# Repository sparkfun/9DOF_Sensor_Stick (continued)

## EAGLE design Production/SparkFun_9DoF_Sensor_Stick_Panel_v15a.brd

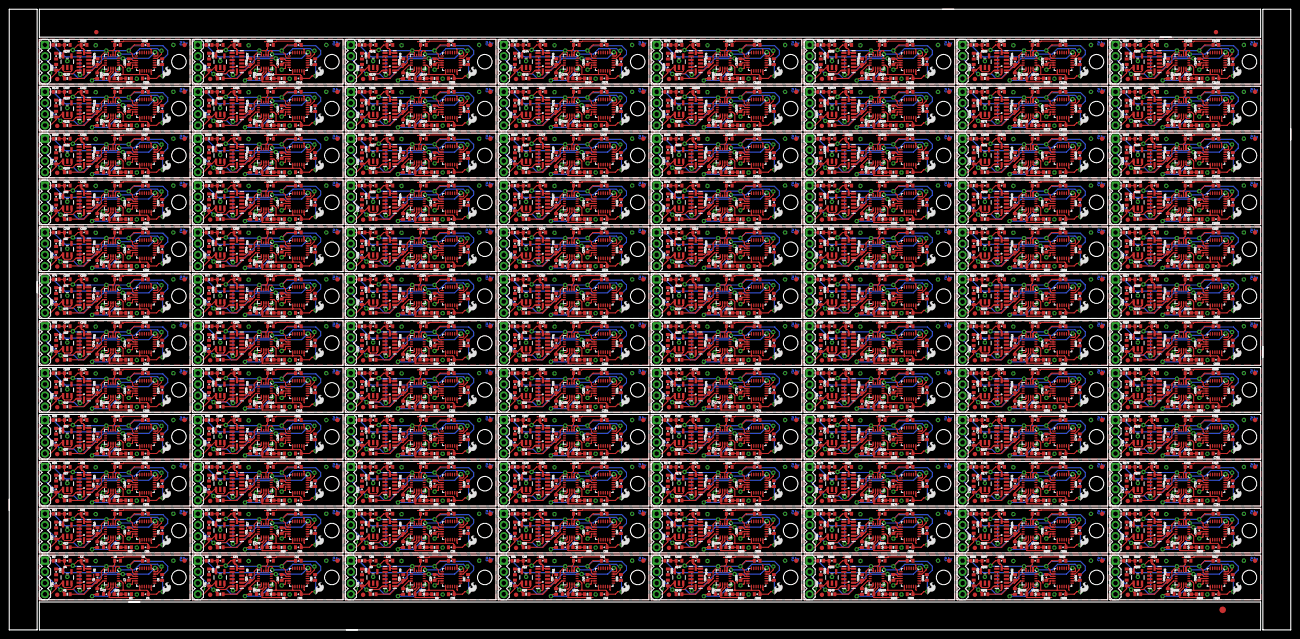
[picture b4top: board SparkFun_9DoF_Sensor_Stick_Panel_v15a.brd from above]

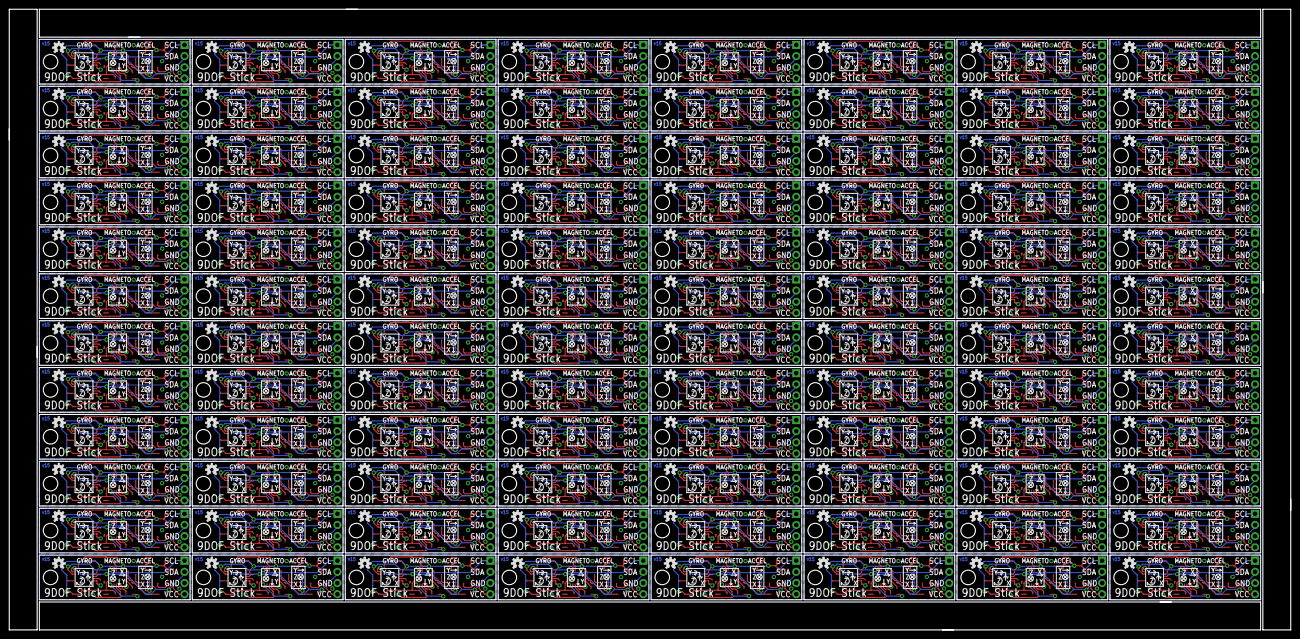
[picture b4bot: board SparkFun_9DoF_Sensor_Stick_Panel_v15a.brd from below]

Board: 2 copper layers, 291.6 x 141.2 mm, 2499 parts (96 on the bottom side), 1056 nets.

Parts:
C1, C2, C5, C7, C9, C10, C13, C14, C16, C18, C19, C24, C25, C26, C28, C30, C31, C36, C37, C38, C40, C42, C43, C48, C49, C50, C52, C54, C55, C60, C61, C62, C64, C66, C67, C72, C73, C74, C76, C78, C79, C84, C85, C86, C88, C90, C91, C96, C97, C98, C100, C102, C103, C108, C109, C110, C112, C114, C115, C120, C121, C122, C124, C126, C127, C132, C133, C134, C136, C138, C139, C144, C145, C146, C148, C150, C151, C156, C157, C158, C160, C162, C163, C168, C169, C170, C172, C174, C175, C180, C181, C182, C184, C186, C187, C192, C193, C194, C196, C198, C199, C204, C205, C206, C208, C210, C211, C216, C217, C218, C220, C222, C223, C228, C229, C230, C232, C234, C235, C240, C241, C242, C244, C246, C247, C252, C253, C254, C256, C258, C259, C264, C265, C266, C268, C270, C271, C276, C277, C278, C280, C282, C283, C288, C289, C290, C292, C294, C295, C300, C301, C302, C304, C306, C307, C312, C313, C314, C316, C318, C319, C324, C325, C326, C328, C330, C331, C336, C337, C338, C340, C342, C343, C348, C349, C350, C352, C354, C355, C360, C361, C362, C364, C366, C367, C372, C373, C374, C376, C378, C379, C384, C385, C386, C388, C390, C391, C396, C397, C398, C400, C402, C403, C408, C409, C410, C412, C414, C415, C420, C421, C422, C424, C426, C427, C432, C433, C434, C436, C438, C439, C444, C445, C446, C448, C450, C451, C456, C457, C458, C460, C462, C463, C468, C469, C470, C472, C474, C475, C480, C481, C482, C484, C486, C487, C492, C493, C494, C496, C498, C499, C504, C505, C506, C508, C510, C511, C516, C517, C518, C520, C522, C523, C528, C529, C530, C532, C534, C535, C540, C541, C542, C544, C546, C547, C552, C553, C554, C556, C558, C559, C564, C565, C566, C568, C570, C571, C576, C577, C578, C580, C582, C583, C588, C589, C590, C592, C594, C595, C600, C601, C602, C604, C606, C607, C612, C613, C614, C616, C618, C619, C624, C625, C626, C628, C630, C631, C636, C637, C638, C640, C642, C643, C648, C649, C650, C652, C654, C655, C660, C661, C662, C664, C666, C667, C672, C673, C674, C676, C678, C679, C684, C685, C686, C688, C690, C691, C696, C697, C698, C700, C702, C703, C708, C709, C710, C712, C714, C715, C720, C721, C722, C724, C726, C727, C732, C733, C734, C736, C738, C739, C744, C745, C746, C748, C750, C751, C756, C757, C758, C760, C762, C763, C768, C769, C770, C772, C774, C775, C780, C781, C782, C784, C786, C787, C792, C793, C794, C796, C798, C799, C804, C805, C806, C808, C810, C811, C816, C817, C818, C820, C822, C823, C828, C829, C830, C832, C834, C835, C840, C841, C842, C844, C846, C847, C852, C853, C854, C856, C858, C859, C864, C865, C866, C868, C870, C871, C876, C877, C878, C880, C882, C883, C888, C889, C890, C892, C894, C895, C900, C901, C902, C904, C906, C907, C912, C913, C914, C916, C918, C919, C924, C925, C926, C928, C930, C931, C936, C937, C938, C940, C942, C943, C948, C949, C950, C952, C954, C955, C960, C961, C962, C964, C966, C967, C972, C973, C974, C976, C978, C979, C984, C985, C986, C988, C990, C991, C996, C997, C998, C1000, C1002, C1003, C1008, C1009, C1010, C1012, C1014, C1015, C1020, C1021, C1022, C1024, C1026, C1027, C1032, C1033, C1034, C1036, C1038, C1039, C1044, C1045, C1046, C1048, C1050, C1051, C1056, C1057, C1058, C1060, C1062, C1063, C1068, C1069, C1070, C1072, C1074, C1075, C1080, C1081, C1082, C1084, C1086, C1087, C1092, C1093, C1094, C1096, C1098, C1099, C1104, C1105, C1106, C1108, C1110, C1111, C1116, C1117, C1118, C1120, C1122, C1123, C1128, C1129, C1130, C1132, C1134, C1135, C1140, C1141, C1142, C1144, C1146, C1147, C1152: 0.1uF; 0402-CAP
C3, C11, C12, C20, C21, C22, C32, C33, C34, C44, C45, C46, C56, C57, C58, C68, C69, C70, C80, C81, C82, C92, C93, C94, C104, C105, C106, C116, C117, C118, C128, C129, C130, C140, C141, C142, C152, C153, C154, C164, C165, C166, C176, C177, C178, C188, C189, C190, C200, C201, C202, C212, C213, C214, C224, C225, C226, C236, C237, C238, C248, C249, C250, C260, C261, C262, C272, C273, C274, C284, C285, C286, C296, C297, C298, C308, C309, C310, C320, C321, C322, C332, C333, C334, C344, C345, C346, C356, C357, C358, C368, C369, C370, C380, C381, C382, C392, C393, C394, C404, C405, C406, C416, C417, C418, C428, C429, C430, C440, C441, C442, C452, C453, C454, C464, C465, C466, C476, C477, C478, C488, C489, C490, C500, C501, C502, C512, C513, C514, C524, C525, C526, C536, C537, C538, C548, C549, C550, C560, C561, C562, C572, C573, C574, C584, C585, C586, C596, C597, C598, C608, C609, C610, C620, C621, C622, C632, C633, C634, C644, C645, C646, C656, C657, C658, C668, C669, C670, C680, C681, C682, C692, C693, C694, C704, C705, C706, C716, C717, C718, C728, C729, C730, C740, C741, C742, C752, C753, C754, C764, C765, C766, C776, C777, C778, C788, C789, C790, C800, C801, C802, C812, C813, C814, C824, C825, C826, C836, C837, C838, C848, C849, C850, C860, C861, C862, C872, C873, C874, C884, C885, C886, C896, C897, C898, C908, C909, C910, C920, C921, C922, C932, C933, C934, C944, C945, C946, C956, C957, C958, C968, C969, C970, C980, C981, C982, C992, C993, C994, C1004, C1005, C1006, C1016, C1017, C1018, C1028, C1029, C1030, C1040, C1041, C1042, C1052, C1053, C1054, C1064, C1065, C1066, C1076, C1077, C1078, C1088, C1089, C1090, C1100, C1101, C1102, C1112, C1113, C1114, C1124, C1125, C1126, C1136, C1137, C1138, C1148, C1149, C1150: 4.7uF; 0402-CAP
C4, C23, C35, C47, C59, C71, C83, C95, C107, C119, C131, C143, C155, C167, C179, C191, C203, C215, C227, C239, C251, C263, C275, C287, C299, C311, C323, C335, C347, C359, C371, C383, C395, C407, C419, C431, C443, C455, C467, C479, C491, C503, C515, C527, C539, C551, C563, C575, C587, C599, C611, C623, C635, C647, C659, C671, C683, C695, C707, C719, C731, C743, C755, C767, C779, C791, C803, C815, C827, C839, C851, C863, C875, C887, C899, C911, C923, C935, C947, C959, C971, C983, C995, C1007, C1019, C1031, C1043, C1055, C1067, C1079, C1091, C1103, C1115, C1127, C1139, C1151: 0.22uF; 0402-CAP
C6, C15, C27, C39, C51, C63, C75, C87, C99, C111, C123, C135, C147, C159, C171, C183, C195, C207, C219, C231, C243, C255, C267, C279, C291, C303, C315, C327, C339, C351, C363, C375, C387, C399, C411, C423, C435, C447, C459, C471, C483, C495, C507, C519, C531, C543, C555, C567, C579, C591, C603, C615, C627, C639, C651, C663, C675, C687, C699, C711, C723, C735, C747, C759, C771, C783, C795, C807, C819, C831, C843, C855, C867, C879, C891, C903, C915, C927, C939, C951, C963, C975, C987, C999, C1011, C1023, C1035, C1047, C1059, C1071, C1083, C1095, C1107, C1119, C1131, C1143: 2.2nF; 0402-CAP
C8, C17, C29, C41, C53, C65, C77, C89, C101, C113, C125, C137, C149, C161, C173, C185, C197, C209, C221, C233, C245, C257, C269, C281, C293, C305, C317, C329, C341, C353, C365, C377, C389, C401, C413, C425, C437, C449, C461, C473, C485, C497, C509, C521, C533, C545, C557, C569, C581, C593, C605, C617, C629, C641, C653, C665, C677, C689, C701, C713, C725, C737, C749, C761, C773, C785, C797, C809, C821, C833, C845, C857, C869, C881, C893, C905, C917, C929, C941, C953, C965, C977, C989, C1001, C1013, C1025, C1037, C1049, C1061, C1073, C1085, C1097, C1109, C1121, C1133, C1145: 10nF; 0402-CAP
E$1: FIDUCIAL-1.5X3
E$5, E$6: FIDUCIAL-1X2
JP1, JP2, JP9, JP10, JP14, JP15, JP19, JP20, JP24, JP25, JP29, JP30, JP34, JP35, JP39, JP40, JP44, JP45, JP49, JP50, JP54, JP55, JP59, JP60, JP64, JP65, JP69, JP70, JP74, JP75, JP79, JP80, JP84, JP85, JP89, JP90, JP94, JP95, JP99, JP100, JP104, JP105, JP109, JP110, JP114, JP115, JP119, JP120, JP124, JP125, JP129, JP130, JP134, JP135, JP139, JP140, JP144, JP145, JP149, JP150, JP154, JP155, JP159, JP160, JP164, JP165, JP169, JP170, JP174, JP175, JP179, JP180, JP184, JP185, JP189, JP190, JP194, JP195, JP199, JP200, JP204, JP205, JP209, JP210, JP214, JP215, JP219, JP220, JP224, JP225, JP229, JP230, JP234, JP235, JP239, JP240, JP244, JP245, JP249, JP250, JP254, JP255, JP259, JP260, JP264, JP265, JP269, JP270, JP274, JP275, JP279, JP280, JP284, JP285, JP289, JP290, JP294, JP295, JP299, JP300, JP304, JP305, JP309, JP310, JP314, JP315, JP319, JP320, JP324, JP325, JP329, JP330, JP334, JP335, JP339, JP340, JP344, JP345, JP349, JP350, JP354, JP355, JP359, JP360, JP364, JP365, JP369, JP370, JP374, JP375, JP379, JP380, JP384, JP385, JP389, JP390, JP394, JP395, JP399, JP400, JP404, JP405, JP409, JP410, JP414, JP415, JP419, JP420, JP424, JP425, JP429, JP430, JP434, JP435, JP439, JP440, JP444, JP445, JP449, JP450, JP454, JP455, JP459, JP460, JP464, JP465, JP469, JP470, JP474, JP475, JP479, JP480: FIDUCIAL1X2; FIDUCIAL-1X2
JP3, JP6, JP11, JP16, JP21, JP26, JP31, JP36, JP41, JP46, JP51, JP56, JP61, JP66, JP71, JP76, JP81, JP86, JP91, JP96, JP101, JP106, JP111, JP116, JP121, JP126, JP131, JP136, JP141, JP146, JP151, JP156, JP161, JP166, JP171, JP176, JP181, JP186, JP191, JP196, JP201, JP206, JP211, JP216, JP221, JP226, JP231, JP236, JP241, JP246, JP251, JP256, JP261, JP266, JP271, JP276, JP281, JP286, JP291, JP296, JP301, JP306, JP311, JP316, JP321, JP326, JP331, JP336, JP341, JP346, JP351, JP356, JP361, JP366, JP371, JP376, JP381, JP386, JP391, JP396, JP401, JP406, JP411, JP416, JP421, JP426, JP431, JP436, JP441, JP446, JP451, JP456, JP461, JP466, JP471, JP476: 1X04
JP4, JP7, JP12, JP17, JP22, JP27, JP32, JP37, JP42, JP47, JP52, JP57, JP62, JP67, JP72, JP77, JP82, JP87, JP92, JP97, JP102, JP107, JP112, JP117, JP122, JP127, JP132, JP137, JP142, JP147, JP152, JP157, JP162, JP167, JP172, JP177, JP182, JP187, JP192, JP197, JP202, JP207, JP212, JP217, JP222, JP227, JP232, JP237, JP242, JP247, JP252, JP257, JP262, JP267, JP272, JP277, JP282, JP287, JP292, JP297, JP302, JP307, JP312, JP317, JP322, JP327, JP332, JP337, JP342, JP347, JP352, JP357, JP362, JP367, JP372, JP377, JP382, JP387, JP392, JP397, JP402, JP407, JP412, JP417, JP422, JP427, JP432, JP437, JP442, JP447, JP452, JP457, JP462, JP467, JP472, JP477: LOGO-SFESK; SFE-LOGO-FLAME
JP5, JP8, JP13, JP18, JP23, JP28, JP33, JP38, JP43, JP48, JP53, JP58, JP63, JP68, JP73, JP78, JP83, JP88, JP93, JP98, JP103, JP108, JP113, JP118, JP123, JP128, JP133, JP138, JP143, JP148, JP153, JP158, JP163, JP168, JP173, JP178, JP183, JP188, JP193, JP198, JP203, JP208, JP213, JP218, JP223, JP228, JP233, JP238, JP243, JP248, JP253, JP258, JP263, JP268, JP273, JP278, JP283, JP288, JP293, JP298, JP303, JP308, JP313, JP318, JP323, JP328, JP333, JP338, JP343, JP348, JP353, JP358, JP363, JP368, JP373, JP378, JP383, JP388, JP393, JP398, JP403, JP408, JP413, JP418, JP423, JP428, JP433, JP438, JP443, JP448, JP453, JP458, JP463, JP468, JP473, JP478: STAND-OFF
LED1, LED2, LED3, LED4, LED5, LED6, LED7, LED8, LED9, LED10, LED11, LED12, LED13, LED14, LED15, LED16, LED17, LED18, LED19, LED20, LED21, LED22, LED23, LED24, LED25, LED26, LED27, LED28, LED29, LED30, LED31, LED32, LED33, LED34, LED35, LED36, LED37, LED38, LED39, LED40, LED41, LED42, LED43, LED44, LED45, LED46, LED47, LED48, LED49, LED50, LED51, LED52, LED53, LED54, LED55, LED56, LED57, LED58, LED59, LED60, LED61, LED62, LED63, LED64, LED65, LED66, LED67, LED68, LED69, LED70, LED71, LED72, LED73, LED74, LED75, LED76, LED77, LED78, LED79, LED80, LED81, LED82, LED83, LED84, LED85, LED86, LED87, LED88, LED89, LED90, LED91, LED92, LED93, LED94, LED95, LED96: Blue; LED-0603
R1, R2, R4, R5, R7, R8, R10, R11, R13, R14, R16, R17, R19, R20, R22, R23, R25, R26, R28, R29, R31, R32, R34, R35, R37, R38, R40, R41, R43, R44, R46, R47, R49, R50, R52, R53, R55, R56, R58, R59, R61, R62, R64, R65, R67, R68, R70, R71, R73, R74, R76, R77, R79, R80, R82, R83, R85, R86, R88, R89, R91, R92, R94, R95, R97, R98, R100, R101, R103, R104, R106, R107, R109, R110, R112, R113, R115, R116, R118, R119, R121, R122, R124, R125, R127, R128, R130, R131, R133, R134, R136, R137, R139, R140, R142, R143, R145, R146, R148, R149, R151, R152, R154, R155, R157, R158, R160, R161, R163, R164, R166, R167, R169, R170, R172, R173, R175, R176, R178, R179, R181, R182, R184, R185, R187, R188, R190, R191, R193, R194, R196, R197, R199, R200, R202, R203, R205, R206, R208, R209, R211, R212, R214, R215, R217, R218, R220, R221, R223, R224, R226, R227, R229, R230, R232, R233, R235, R236, R238, R239, R241, R242, R244, R245, R247, R248, R250, R251, R253, R254, R256, R257, R259, R260, R262, R263, R265, R266, R268, R269, R271, R272, R274, R275, R277, R278, R280, R281, R283, R284, R286, R287: 4.7K; 0402-RES
R3, R6, R9, R12, R15, R18, R21, R24, R27, R30, R33, R36, R39, R42, R45, R48, R51, R54, R57, R60, R63, R66, R69, R72, R75, R78, R81, R84, R87, R90, R93, R96, R99, R102, R105, R108, R111, R114, R117, R120, R123, R126, R129, R132, R135, R138, R141, R144, R147, R150, R153, R156, R159, R162, R165, R168, R171, R174, R177, R180, R183, R186, R189, R192, R195, R198, R201, R204, R207, R210, R213, R216, R219, R222, R225, R228, R231, R234, R237, R240, R243, R246, R249, R252, R255, R258, R261, R264, R267, R270, R273, R276, R279, R282, R285, R288: 330; 0402-RES
U1, U3, U7, U10, U13, U16, U19, U22, U25, U28, U31, U34, U37, U40, U43, U46, U49, U52, U55, U58, U61, U64, U67, U70, U73, U76, U79, U82, U85, U88, U91, U94, U97, U100, U103, U106, U109, U112, U115, U118, U121, U124, U127, U130, U133, U136, U139, U142, U145, U148, U151, U154, U157, U160, U163, U166, U169, U172, U175, U178, U181, U184, U187, U190, U193, U196, U199, U202, U205, U208, U211, U214, U217, U220, U223, U226, U229, U232, U235, U238, U241, U244, U247, U250, U253, U256, U259, U262, U265, U268, U271, U274, U277, U280, U283, U286: ITG-32001:1; QFN-24_1:1
U2, U5, U8, U11, U14, U17, U20, U23, U26, U29, U32, U35, U38, U41, U44, U47, U50, U53, U56, U59, U62, U65, U68, U71, U74, U77, U80, U83, U86, U89, U92, U95, U98, U101, U104, U107, U110, U113, U116, U119, U122, U125, U128, U131, U134, U137, U140, U143, U146, U149, U152, U155, U158, U161, U164, U167, U170, U173, U176, U179, U182, U185, U188, U191, U194, U197, U200, U203, U206, U209, U212, U215, U218, U221, U224, U227, U230, U233, U236, U239, U242, U245, U248, U251, U254, U257, U260, U263, U266, U269, U272, U275, U278, U281, U284, U287: ADXL345; LGA14
U4, U6, U9, U12, U15, U18, U21, U24, U27, U30, U33, U36, U39, U42, U45, U48, U51, U54, U57, U60, U63, U66, U69, U72, U75, U78, U81, U84, U87, U90, U93, U96, U99, U102, U105, U108, U111, U114, U117, U120, U123, U126, U129, U132, U135, U138, U141, U144, U147, U150, U153, U156, U159, U162, U165, U168, U171, U174, U177, U180, U183, U186, U189, U192, U195, U198, U201, U204, U207, U210, U213, U216, U219, U222, U225, U228, U231, U234, U237, U240, U243, U246, U249, U252, U255, U258, U261, U264, U267, U270, U273, U276, U279, U282, U285, U288: 3.3V; SOT23-5
U$1, U$2, U$5, U$7, U$9, U$11, U$13, U$15, U$17, U$19, U$21, U$23, U$25, U$27, U$29, U$31, U$33, U$35, U$37, U$39, U$41, U$43, U$45, U$47, U$49, U$51, U$53, U$55, U$57, U$59, U$61, U$63, U$65, U$67, U$69, U$71, U$73, U$75, U$77, U$79, U$81, U$83, U$85, U$87, U$89, U$91, U$93, U$95, U$97, U$99, U$101, U$103, U$105, U$107, U$109, U$111, U$113, U$115, U$117, U$119, U$121, U$123, U$125, U$127, U$129, U$131, U$133, U$135, U$137, U$139, U$141, U$143, U$145, U$147, U$149, U$151, U$153, U$155, U$157, U$159, U$161, U$163, U$165, U$167, U$169, U$171, U$173, U$175, U$177, U$179, U$181, U$183, U$185, U$187, U$189, U$191: HMC5883L1:1; 16LPCC_1:1
U$3, U$4, U$6, U$8, U$10, U$12, U$14, U$16, U$18, U$20, U$22, U$24, U$26, U$28, U$30, U$32, U$34, U$36, U$38, U$40, U$42, U$44, U$46, U$48, U$50, U$52, U$54, U$56, U$58, U$60, U$62, U$64, U$66, U$68, U$70, U$72, U$74, U$76, U$78, U$80, U$82, U$84, U$86, U$88, U$90, U$92, U$94, U$96, U$98, U$100, U$102, U$104, U$106, U$108, U$110, U$112, U$114, U$116, U$118, U$120, U$122, U$124, U$126, U$128, U$130, U$132, U$134, U$136, U$138, U$140, U$142, U$144, U$146, U$148, U$150, U$152, U$154, U$156, U$158, U$160, U$162, U$164, U$166, U$168, U$170, U$172, U$174, U$176, U$178, U$180, U$182, U$184, U$186, U$188, U$190, U$192: OSHW-LOGOS; OSHW-LOGO-S

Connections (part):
3.3V: C1.1, C2.1, C5.1, C8.1, C9.1, C10.1, C12.1, LED1.A, R1.2, R2.2, U1.8, U1.13, U2.1, U2.6, U2.7, U4.5, U$2.2, U$2.4, U$2.13
3.3V1: C13.1, C14.1, C17.1, C18.1, C19.1, C20.1, C24.1, LED2.A, R4.2, R5.2, U3.8, U3.13, U5.1, U5.6, U5.7, U6.5, U$1.2, U$1.4, U$1.13
3.3V2: C25.1, C26.1, C29.1, C30.1, C31.1, C32.1, C36.1, LED3.A, R7.2, R8.2, U7.8, U7.13, U8.1, U8.6, U8.7, U9.5, U$5.2, U$5.4, U$5.13
3.3V3: C37.1, C38.1, C41.1, C42.1, C43.1, C44.1, C48.1, LED4.A, R10.2, R11.2, U10.8, U10.13, U11.1, U11.6, U11.7, U12.5, U$7.2, U$7.4, U$7.13
3.3V4: C49.1, C50.1, C53.1, C54.1, C55.1, C56.1, C60.1, LED5.A, R13.2, R14.2, U13.8, U13.13, U14.1, U14.6, U14.7, U15.5, U$9.2, U$9.4, U$9.13
3.3V5: C61.1, C62.1, C65.1, C66.1, C67.1, C68.1, C72.1, LED6.A, R16.2, R17.2, U16.8, U16.13, U17.1, U17.6, U17.7, U18.5, U$11.2, U$11.4, U$11.13
3.3V6: C73.1, C74.1, C77.1, C78.1, C79.1, C80.1, C84.1, LED7.A, R19.2, R20.2, U19.8, U19.13, U20.1, U20.6, U20.7, U21.5, U$13.2, U$13.4, U$13.13
3.3V7: C85.1, C86.1, C89.1, C90.1, C91.1, C92.1, C96.1, LED8.A, R22.2, R23.2, U22.8, U22.13, U23.1, U23.6, U23.7, U24.5, U$15.2, U$15.4, U$15.13
3.3V8: C97.1, C98.1, C101.1, C102.1, C103.1, C104.1, C108.1, LED9.A, R25.2, R26.2, U25.8, U25.13, U26.1, U26.6, U26.7, U27.5, U$17.2, U$17.4, U$17.13
3.3V9: C109.1, C110.1, C113.1, C114.1, C115.1, C116.1, C120.1, LED10.A, R28.2, R29.2, U28.8, U28.13, U29.1, U29.6, U29.7, U30.5, U$19.2, U$19.4, U$19.13
3.3V10: C121.1, C122.1, C125.1, C126.1, C127.1, C128.1, C132.1, LED11.A, R31.2, R32.2, U31.8, U31.13, U32.1, U32.6, U32.7, U33.5, U$21.2, U$21.4, U$21.13
3.3V11: C133.1, C134.1, C137.1, C138.1, C139.1, C140.1, C144.1, LED12.A, R34.2, R35.2, U34.8, U34.13, U35.1, U35.6, U35.7, U36.5, U$23.2, U$23.4, U$23.13
3.3V12: C145.1, C146.1, C149.1, C150.1, C151.1, C152.1, C156.1, LED13.A, R37.2, R38.2, U37.8, U37.13, U38.1, U38.6, U38.7, U39.5, U$25.2, U$25.4, U$25.13
3.3V13: C157.1, C158.1, C161.1, C162.1, C163.1, C164.1, C168.1, LED14.A, R40.2, R41.2, U40.8, U40.13, U41.1, U41.6, U41.7, U42.5, U$27.2, U$27.4, U$27.13
3.3V14: C169.1, C170.1, C173.1, C174.1, C175.1, C176.1, C180.1, LED15.A, R43.2, R44.2, U43.8, U43.13, U44.1, U44.6, U44.7, U45.5, U$29.2, U$29.4, U$29.13
3.3V15: C181.1, C182.1, C185.1, C186.1, C187.1, C188.1, C192.1, LED16.A, R46.2, R47.2, U46.8, U46.13, U47.1, U47.6, U47.7, U48.5, U$31.2, U$31.4, U$31.13
3.3V16: C193.1, C194.1, C197.1, C198.1, C199.1, C200.1, C204.1, LED17.A, R49.2, R50.2, U49.8, U49.13, U50.1, U50.6, U50.7, U51.5, U$33.2, U$33.4, U$33.13
3.3V17: C205.1, C206.1, C209.1, C210.1, C211.1, C212.1, C216.1, LED18.A, R52.2, R53.2, U52.8, U52.13, U53.1, U53.6, U53.7, U54.5, U$35.2, U$35.4, U$35.13
3.3V18: C217.1, C218.1, C221.1, C222.1, C223.1, C224.1, C228.1, LED19.A, R55.2, R56.2, U55.8, U55.13, U56.1, U56.6, U56.7, U57.5, U$37.2, U$37.4, U$37.13
3.3V19: C229.1, C230.1, C233.1, C234.1, C235.1, C236.1, C240.1, LED20.A, R58.2, R59.2, U58.8, U58.13, U59.1, U59.6, U59.7, U60.5, U$39.2, U$39.4, U$39.13
3.3V20: C241.1, C242.1, C245.1, C246.1, C247.1, C248.1, C252.1, LED21.A, R61.2, R62.2, U61.8, U61.13, U62.1, U62.6, U62.7, U63.5, U$41.2, U$41.4, U$41.13
3.3V21: C253.1, C254.1, C257.1, C258.1, C259.1, C260.1, C264.1, LED22.A, R64.2, R65.2, U64.8, U64.13, U65.1, U65.6, U65.7, U66.5, U$43.2, U$43.4, U$43.13
3.3V22: C265.1, C266.1, C269.1, C270.1, C271.1, C272.1, C276.1, LED23.A, R67.2, R68.2, U67.8, U67.13, U68.1, U68.6, U68.7, U69.5, U$45.2, U$45.4, U$45.13
3.3V23: C277.1, C278.1, C281.1, C282.1, C283.1, C284.1, C288.1, LED24.A, R70.2, R71.2, U70.8, U70.13, U71.1, U71.6, U71.7, U72.5, U$47.2, U$47.4, U$47.13
3.3V24: C289.1, C290.1, C293.1, C294.1, C295.1, C296.1, C300.1, LED25.A, R73.2, R74.2, U73.8, U73.13, U74.1, U74.6, U74.7, U75.5, U$49.2, U$49.4, U$49.13
3.3V25: C301.1, C302.1, C305.1, C306.1, C307.1, C308.1, C312.1, LED26.A, R76.2, R77.2, U76.8, U76.13, U77.1, U77.6, U77.7, U78.5, U$51.2, U$51.4, U$51.13
3.3V26: C313.1, C314.1, C317.1, C318.1, C319.1, C320.1, C324.1, LED27.A, R79.2, R80.2, U79.8, U79.13, U80.1, U80.6, U80.7, U81.5, U$53.2, U$53.4, U$53.13
3.3V27: C325.1, C326.1, C329.1, C330.1, C331.1, C332.1, C336.1, LED28.A, R82.2, R83.2, U82.8, U82.13, U83.1, U83.6, U83.7, U84.5, U$55.2, U$55.4, U$55.13
3.3V28: C337.1, C338.1, C341.1, C342.1, C343.1, C344.1, C348.1, LED29.A, R85.2, R86.2, U85.8, U85.13, U86.1, U86.6, U86.7, U87.5, U$57.2, U$57.4, U$57.13
3.3V29: C349.1, C350.1, C353.1, C354.1, C355.1, C356.1, C360.1, LED30.A, R88.2, R89.2, U88.8, U88.13, U89.1, U89.6, U89.7, U90.5, U$59.2, U$59.4, U$59.13
3.3V30: C361.1, C362.1, C365.1, C366.1, C367.1, C368.1, C372.1, LED31.A, R91.2, R92.2, U91.8, U91.13, U92.1, U92.6, U92.7, U93.5, U$61.2, U$61.4, U$61.13
3.3V31: C373.1, C374.1, C377.1, C378.1, C379.1, C380.1, C384.1, LED32.A, R94.2, R95.2, U94.8, U94.13, U95.1, U95.6, U95.7, U96.5, U$63.2, U$63.4, U$63.13
3.3V32: C385.1, C386.1, C389.1, C390.1, C391.1, C392.1, C396.1, LED33.A, R97.2, R98.2, U97.8, U97.13, U98.1, U98.6, U98.7, U99.5, U$65.2, U$65.4, U$65.13
3.3V33: C397.1, C398.1, C401.1, C402.1, C403.1, C404.1, C408.1, LED34.A, R100.2, R101.2, U100.8, U100.13, U101.1, U101.6, U101.7, U102.5, U$67.2, U$67.4, U$67.13
3.3V34: C409.1, C410.1, C413.1, C414.1, C415.1, C416.1, C420.1, LED35.A, R103.2, R104.2, U103.8, U103.13, U104.1, U104.6, U104.7, U105.5, U$69.2, U$69.4, U$69.13
3.3V35: C421.1, C422.1, C425.1, C426.1, C427.1, C428.1, C432.1, LED36.A, R106.2, R107.2, U106.8, U106.13, U107.1, U107.6, U107.7, U108.5, U$71.2, U$71.4, U$71.13
3.3V36: C433.1, C434.1, C437.1, C438.1, C439.1, C440.1, C444.1, LED37.A, R109.2, R110.2, U109.8, U109.13, U110.1, U110.6, U110.7, U111.5, U$73.2, U$73.4, U$73.13
3.3V37: C445.1, C446.1, C449.1, C450.1, C451.1, C452.1, C456.1, LED38.A, R112.2, R113.2, U112.8, U112.13, U113.1, U113.6, U113.7, U114.5, U$75.2, U$75.4, U$75.13
3.3V38: C457.1, C458.1, C461.1, C462.1, C463.1, C464.1, C468.1, LED39.A, R115.2, R116.2, U115.8, U115.13, U116.1, U116.6, U116.7, U117.5, U$77.2, U$77.4, U$77.13
3.3V39: C469.1, C470.1, C473.1, C474.1, C475.1, C476.1, C480.1, LED40.A, R118.2, R119.2, U118.8, U118.13, U119.1, U119.6, U119.7, U120.5, U$79.2, U$79.4, U$79.13
3.3V40: C481.1, C482.1, C485.1, C486.1, C487.1, C488.1, C492.1, LED41.A, R121.2, R122.2, U121.8, U121.13, U122.1, U122.6, U122.7, U123.5, U$81.2, U$81.4, U$81.13
3.3V41: C493.1, C494.1, C497.1, C498.1, C499.1, C500.1, C504.1, LED42.A, R124.2, R125.2, U124.8, U124.13, U125.1, U125.6, U125.7, U126.5, U$83.2, U$83.4, U$83.13
3.3V42: C505.1, C506.1, C509.1, C510.1, C511.1, C512.1, C516.1, LED43.A, R127.2, R128.2, U127.8, U127.13, U128.1, U128.6, U128.7, U129.5, U$85.2, U$85.4, U$85.13
3.3V43: C517.1, C518.1, C521.1, C522.1, C523.1, C524.1, C528.1, LED44.A, R130.2, R131.2, U130.8, U130.13, U131.1, U131.6, U131.7, U132.5, U$87.2, U$87.4, U$87.13
3.3V44: C529.1, C530.1, C533.1, C534.1, C535.1, C536.1, C540.1, LED45.A, R133.2, R134.2, U133.8, U133.13, U134.1, U134.6, U134.7, U135.5, U$89.2, U$89.4, U$89.13
3.3V45: C541.1, C542.1, C545.1, C546.1, C547.1, C548.1, C552.1, LED46.A, R136.2, R137.2, U136.8, U136.13, U137.1, U137.6, U137.7, U138.5, U$91.2, U$91.4, U$91.13
3.3V46: C553.1, C554.1, C557.1, C558.1, C559.1, C560.1, C564.1, LED47.A, R139.2, R140.2, U139.8, U139.13, U140.1, U140.6, U140.7, U141.5, U$93.2, U$93.4, U$93.13
3.3V47: C565.1, C566.1, C569.1, C570.1, C571.1, C572.1, C576.1, LED48.A, R142.2, R143.2, U142.8, U142.13, U143.1, U143.6, U143.7, U144.5, U$95.2, U$95.4, U$95.13
3.3V48: C577.1, C578.1, C581.1, C582.1, C583.1, C584.1, C588.1, LED49.A, R145.2, R146.2, U145.8, U145.13, U146.1, U146.6, U146.7, U147.5, U$97.2, U$97.4, U$97.13
3.3V49: C589.1, C590.1, C593.1, C594.1, C595.1, C596.1, C600.1, LED50.A, R148.2, R149.2, U148.8, U148.13, U149.1, U149.6, U149.7, U150.5, U$99.2, U$99.4, U$99.13
3.3V50: C601.1, C602.1, C605.1, C606.1, C607.1, C608.1, C612.1, LED51.A, R151.2, R152.2, U151.8, U151.13, U152.1, U152.6, U152.7, U153.5, U$101.2, U$101.4, U$101.13
3.3V51: C613.1, C614.1, C617.1, C618.1, C619.1, C620.1, C624.1, LED52.A, R154.2, R155.2, U154.8, U154.13, U155.1, U155.6, U155.7, U156.5, U$103.2, U$103.4, U$103.13
3.3V52: C625.1, C626.1, C629.1, C630.1, C631.1, C632.1, C636.1, LED53.A, R157.2, R158.2, U157.8, U157.13, U158.1, U158.6, U158.7, U159.5, U$105.2, U$105.4, U$105.13
3.3V53: C637.1, C638.1, C641.1, C642.1, C643.1, C644.1, C648.1, LED54.A, R160.2, R161.2, U160.8, U160.13, U161.1, U161.6, U161.7, U162.5, U$107.2, U$107.4, U$107.13
3.3V54: C649.1, C650.1, C653.1, C654.1, C655.1, C656.1, C660.1, LED55.A, R163.2, R164.2, U163.8, U163.13, U164.1, U164.6, U164.7, U165.5, U$109.2, U$109.4, U$109.13
3.3V55: C661.1, C662.1, C665.1, C666.1, C667.1, C668.1, C672.1, LED56.A, R166.2, R167.2, U166.8, U166.13, U167.1, U167.6, U167.7, U168.5, U$111.2, U$111.4, U$111.13
3.3V56: C673.1, C674.1, C677.1, C678.1, C679.1, C680.1, C684.1, LED57.A, R169.2, R170.2, U169.8, U169.13, U170.1, U170.6, U170.7, U171.5, U$113.2, U$113.4, U$113.13
3.3V57: C685.1, C686.1, C689.1, C690.1, C691.1, C692.1, C696.1, LED58.A, R172.2, R173.2, U172.8, U172.13, U173.1, U173.6, U173.7, U174.5, U$115.2, U$115.4, U$115.13
3.3V58: C697.1, C698.1, C701.1, C702.1, C703.1, C704.1, C708.1, LED59.A, R175.2, R176.2, U175.8, U175.13, U176.1, U176.6, U176.7, U177.5, U$117.2, U$117.4, U$117.13
3.3V59: C709.1, C710.1, C713.1, C714.1, C715.1, C716.1, C720.1, LED60.A, R178.2, R179.2, U178.8, U178.13, U179.1, U179.6, U179.7, U180.5, U$119.2, U$119.4, U$119.13
3.3V60: C721.1, C722.1, C725.1, C726.1, C727.1, C728.1, C732.1, LED61.A, R181.2, R182.2, U181.8, U181.13, U182.1, U182.6, U182.7, U183.5, U$121.2, U$121.4, U$121.13
3.3V61: C733.1, C734.1, C737.1, C738.1, C739.1, C740.1, C744.1, LED62.A, R184.2, R185.2, U184.8, U184.13, U185.1, U185.6, U185.7, U186.5, U$123.2, U$123.4, U$123.13
3.3V62: C745.1, C746.1, C749.1, C750.1, C751.1, C752.1, C756.1, LED63.A, R187.2, R188.2, U187.8, U187.13, U188.1, U188.6, U188.7, U189.5, U$125.2, U$125.4, U$125.13
3.3V63: C757.1, C758.1, C761.1, C762.1, C763.1, C764.1, C768.1, LED64.A, R190.2, R191.2, U190.8, U190.13, U191.1, U191.6, U191.7, U192.5, U$127.2, U$127.4, U$127.13
3.3V64: C769.1, C770.1, C773.1, C774.1, C775.1, C776.1, C780.1, LED65.A, R193.2, R194.2, U193.8, U193.13, U194.1, U194.6, U194.7, U195.5, U$129.2, U$129.4, U$129.13
3.3V65: C781.1, C782.1, C785.1, C786.1, C787.1, C788.1, C792.1, LED66.A, R196.2, R197.2, U196.8, U196.13, U197.1, U197.6, U197.7, U198.5, U$131.2, U$131.4, U$131.13
3.3V66: C793.1, C794.1, C797.1, C798.1, C799.1, C800.1, C804.1, LED67.A, R199.2, R200.2, U199.8, U199.13, U200.1, U200.6, U200.7, U201.5, U$133.2, U$133.4, U$133.13
3.3V67: C805.1, C806.1, C809.1, C810.1, C811.1, C812.1, C816.1, LED68.A, R202.2, R203.2, U202.8, U202.13, U203.1, U203.6, U203.7, U204.5, U$135.2, U$135.4, U$135.13
3.3V68: C817.1, C818.1, C821.1, C822.1, C823.1, C824.1, C828.1, LED69.A, R205.2, R206.2, U205.8, U205.13, U206.1, U206.6, U206.7, U207.5, U$137.2, U$137.4, U$137.13
3.3V69: C829.1, C830.1, C833.1, C834.1, C835.1, C836.1, C840.1, LED70.A, R208.2, R209.2, U208.8, U208.13, U209.1, U209.6, U209.7, U210.5, U$139.2, U$139.4, U$139.13
3.3V70: C841.1, C842.1, C845.1, C846.1, C847.1, C848.1, C852.1, LED71.A, R211.2, R212.2, U211.8, U211.13, U212.1, U212.6, U212.7, U213.5, U$141.2, U$141.4, U$141.13
3.3V71: C853.1, C854.1, C857.1, C858.1, C859.1, C860.1, C864.1, LED72.A, R214.2, R215.2, U214.8, U214.13, U215.1, U215.6, U215.7, U216.5, U$143.2, U$143.4, U$143.13
3.3V72: C865.1, C866.1, C869.1, C870.1, C871.1, C872.1, C876.1, LED73.A, R217.2, R218.2, U217.8, U217.13, U218.1, U218.6, U218.7, U219.5, U$145.2, U$145.4, U$145.13
3.3V73: C877.1, C878.1, C881.1, C882.1, C883.1, C884.1, C888.1, LED74.A, R220.2, R221.2, U220.8, U220.13, U221.1, U221.6, U221.7, U222.5, U$147.2, U$147.4, U$147.13
3.3V74: C889.1, C890.1, C893.1, C894.1, C895.1, C896.1, C900.1, LED75.A, R223.2, R224.2, U223.8, U223.13, U224.1, U224.6, U224.7, U225.5, U$149.2, U$149.4, U$149.13
3.3V75: C901.1, C902.1, C905.1, C906.1, C907.1, C908.1, C912.1, LED76.A, R226.2, R227.2, U226.8, U226.13, U227.1, U227.6, U227.7, U228.5, U$151.2, U$151.4, U$151.13
3.3V76: C913.1, C914.1, C917.1, C918.1, C919.1, C920.1, C924.1, LED77.A, R229.2, R230.2, U229.8, U229.13, U230.1, U230.6, U230.7, U231.5, U$153.2, U$153.4, U$153.13
3.3V77: C925.1, C926.1, C929.1, C930.1, C931.1, C932.1, C936.1, LED78.A, R232.2, R233.2, U232.8, U232.13, U233.1, U233.6, U233.7, U234.5, U$155.2, U$155.4, U$155.13
3.3V78: C937.1, C938.1, C941.1, C942.1, C943.1, C944.1, C948.1, LED79.A, R235.2, R236.2, U235.8, U235.13, U236.1, U236.6, U236.7, U237.5, U$157.2, U$157.4, U$157.13
3.3V79: C949.1, C950.1, C953.1, C954.1, C955.1, C956.1, C960.1, LED80.A, R238.2, R239.2, U238.8, U238.13, U239.1, U239.6, U239.7, U240.5, U$159.2, U$159.4, U$159.13
3.3V80: C961.1, C962.1, C965.1, C966.1, C967.1, C968.1, C972.1, LED81.A, R241.2, R242.2, U241.8, U241.13, U242.1, U242.6, U242.7, U243.5, U$161.2, U$161.4, U$161.13
3.3V81: C973.1, C974.1, C977.1, C978.1, C979.1, C980.1, C984.1, LED82.A, R244.2, R245.2, U244.8, U244.13, U245.1, U245.6, U245.7, U246.5, U$163.2, U$163.4, U$163.13
3.3V82: C985.1, C986.1, C989.1, C990.1, C991.1, C992.1, C996.1, LED83.A, R247.2, R248.2, U247.8, U247.13, U248.1, U248.6, U248.7, U249.5, U$165.2, U$165.4, U$165.13
3.3V83: C997.1, C998.1, C1001.1, C1002.1, C1003.1, C1004.1, C1008.1, LED84.A, R250.2, R251.2, U250.8, U250.13, U251.1, U251.6, U251.7, U252.5, U$167.2, U$167.4, U$167.13
3.3V84: C1009.1, C1010.1, C1013.1, C1014.1, C1015.1, C1016.1, C1020.1, LED85.A, R253.2, R254.2, U253.8, U253.13, U254.1, U254.6, U254.7, U255.5, U$169.2, U$169.4, U$169.13
3.3V85: C1021.1, C1022.1, C1025.1, C1026.1, C1027.1, C1028.1, C1032.1, LED86.A, R256.2, R257.2, U256.8, U256.13, U257.1, U257.6, U257.7, U258.5, U$171.2, U$171.4, U$171.13
3.3V86: C1033.1, C1034.1, C1037.1, C1038.1, C1039.1, C1040.1, C1044.1, LED87.A, R259.2, R260.2, U259.8, U259.13, U260.1, U260.6, U260.7, U261.5, U$173.2, U$173.4, U$173.13
3.3V87: C1045.1, C1046.1, C1049.1, C1050.1, C1051.1, C1052.1, C1056.1, LED88.A, R262.2, R263.2, U262.8, U262.13, U263.1, U263.6, U263.7, U264.5, U$175.2, U$175.4, U$175.13
3.3V88: C1057.1, C1058.1, C1061.1, C1062.1, C1063.1, C1064.1, C1068.1, LED89.A, R265.2, R266.2, U265.8, U265.13, U266.1, U266.6, U266.7, U267.5, U$177.2, U$177.4, U$177.13
3.3V89: C1069.1, C1070.1, C1073.1, C1074.1, C1075.1, C1076.1, C1080.1, LED90.A, R268.2, R269.2, U268.8, U268.13, U269.1, U269.6, U269.7, U270.5, U$179.2, U$179.4, U$179.13
3.3V90: C1081.1, C1082.1, C1085.1, C1086.1, C1087.1, C1088.1, C1092.1, LED91.A, R271.2, R272.2, U271.8, U271.13, U272.1, U272.6, U272.7, U273.5, U$181.2, U$181.4, U$181.13
3.3V91: C1093.1, C1094.1, C1097.1, C1098.1, C1099.1, C1100.1, C1104.1, LED92.A, R274.2, R275.2, U274.8, U274.13, U275.1, U275.6, U275.7, U276.5, U$183.2, U$183.4, U$183.13
3.3V92: C1105.1, C1106.1, C1109.1, C1110.1, C1111.1, C1112.1, C1116.1, LED93.A, R277.2, R278.2, U277.8, U277.13, U278.1, U278.6, U278.7, U279.5, U$185.2, U$185.4, U$185.13
3.3V93: C1117.1, C1118.1, C1121.1, C1122.1, C1123.1, C1124.1, C1128.1, LED94.A, R280.2, R281.2, U280.8, U280.13, U281.1, U281.6, U281.7, U282.5, U$187.2, U$187.4, U$187.13
3.3V94: C1129.1, C1130.1, C1133.1, C1134.1, C1135.1, C1136.1, C1140.1, LED95.A, R283.2, R284.2, U283.8, U283.13, U284.1, U284.6, U284.7, U285.5, U$189.2, U$189.4, U$189.13
3.3V95: C1141.1, C1142.1, C1145.1, C1146.1, C1147.1, C1148.1, C1152.1, LED96.A, R286.2, R287.2, U286.8, U286.13, U287.1, U287.6, U287.7, U288.5, U$191.2, U$191.4, U$191.13
GND: C1.2, C2.2, C3.2, C5.2, C6.2, C7.2, C8.2, C9.2, C10.2, C11.2, C12.2, JP3.3, R3.1, U1.1, U1.9, U1.11, U1.18, U2.2, U2.4, U2.5, U2.12, U4.2, U$2.9, U$2.11
GND1: C13.2, C14.2, C15.2, C16.2, C17.2, C18.2, C19.2, C20.2, C21.2, C22.2, C24.2, JP6.3, R6.1, U3.1, U3.9, U3.11, U3.18, U5.2, U5.4, U5.5, U5.12, U6.2, U$1.9, U$1.11
GND2: C25.2, C26.2, C27.2, C28.2, C29.2, C30.2, C31.2, C32.2, C33.2, C34.2, C36.2, JP11.3, R9.1, U7.1, U7.9, U7.11, U7.18, U8.2, U8.4, U8.5, U8.12, U9.2, U$5.9, U$5.11
GND3: C37.2, C38.2, C39.2, C40.2, C41.2, C42.2, C43.2, C44.2, C45.2, C46.2, C48.2, JP16.3, R12.1, U10.1, U10.9, U10.11, U10.18, U11.2, U11.4, U11.5, U11.12, U12.2, U$7.9, U$7.11
GND4: C49.2, C50.2, C51.2, C52.2, C53.2, C54.2, C55.2, C56.2, C57.2, C58.2, C60.2, JP21.3, R15.1, U13.1, U13.9, U13.11, U13.18, U14.2, U14.4, U14.5, U14.12, U15.2, U$9.9, U$9.11
GND5: C61.2, C62.2, C63.2, C64.2, C65.2, C66.2, C67.2, C68.2, C69.2, C70.2, C72.2, JP26.3, R18.1, U16.1, U16.9, U16.11, U16.18, U17.2, U17.4, U17.5, U17.12, U18.2, U$11.9, U$11.11
GND6: C73.2, C74.2, C75.2, C76.2, C77.2, C78.2, C79.2, C80.2, C81.2, C82.2, C84.2, JP31.3, R21.1, U19.1, U19.9, U19.11, U19.18, U20.2, U20.4, U20.5, U20.12, U21.2, U$13.9, U$13.11
GND7: C85.2, C86.2, C87.2, C88.2, C89.2, C90.2, C91.2, C92.2, C93.2, C94.2, C96.2, JP36.3, R24.1, U22.1, U22.9, U22.11, U22.18, U23.2, U23.4, U23.5, U23.12, U24.2, U$15.9, U$15.11
GND8: C97.2, C98.2, C99.2, C100.2, C101.2, C102.2, C103.2, C104.2, C105.2, C106.2, C108.2, JP41.3, R27.1, U25.1, U25.9, U25.11, U25.18, U26.2, U26.4, U26.5, U26.12, U27.2, U$17.9, U$17.11
GND9: C109.2, C110.2, C111.2, C112.2, C113.2, C114.2, C115.2, C116.2, C117.2, C118.2, C120.2, JP46.3, R30.1, U28.1, U28.9, U28.11, U28.18, U29.2, U29.4, U29.5, U29.12, U30.2, U$19.9, U$19.11
GND10: C121.2, C122.2, C123.2, C124.2, C125.2, C126.2, C127.2, C128.2, C129.2, C130.2, C132.2, JP51.3, R33.1, U31.1, U31.9, U31.11, U31.18, U32.2, U32.4, U32.5, U32.12, U33.2, U$21.9, U$21.11
GND11: C133.2, C134.2, C135.2, C136.2, C137.2, C138.2, C139.2, C140.2, C141.2, C142.2, C144.2, JP56.3, R36.1, U34.1, U34.9, U34.11, U34.18, U35.2, U35.4, U35.5, U35.12, U36.2, U$23.9, U$23.11
GND12: C145.2, C146.2, C147.2, C148.2, C149.2, C150.2, C151.2, C152.2, C153.2, C154.2, C156.2, JP61.3, R39.1, U37.1, U37.9, U37.11, U37.18, U38.2, U38.4, U38.5, U38.12, U39.2, U$25.9, U$25.11
GND13: C157.2, C158.2, C159.2, C160.2, C161.2, C162.2, C163.2, C164.2, C165.2, C166.2, C168.2, JP66.3, R42.1, U40.1, U40.9, U40.11, U40.18, U41.2, U41.4, U41.5, U41.12, U42.2, U$27.9, U$27.11
GND14: C169.2, C170.2, C171.2, C172.2, C173.2, C174.2, C175.2, C176.2, C177.2, C178.2, C180.2, JP71.3, R45.1, U43.1, U43.9, U43.11, U43.18, U44.2, U44.4, U44.5, U44.12, U45.2, U$29.9, U$29.11
GND15: C181.2, C182.2, C183.2, C184.2, C185.2, C186.2, C187.2, C188.2, C189.2, C190.2, C192.2, JP76.3, R48.1, U46.1, U46.9, U46.11, U46.18, U47.2, U47.4, U47.5, U47.12, U48.2, U$31.9, U$31.11
GND16: C193.2, C194.2, C195.2, C196.2, C197.2, C198.2, C199.2, C200.2, C201.2, C202.2, C204.2, JP81.3, R51.1, U49.1, U49.9, U49.11, U49.18, U50.2, U50.4, U50.5, U50.12, U51.2, U$33.9, U$33.11
GND17: C205.2, C206.2, C207.2, C208.2, C209.2, C210.2, C211.2, C212.2, C213.2, C214.2, C216.2, JP86.3, R54.1, U52.1, U52.9, U52.11, U52.18, U53.2, U53.4, U53.5, U53.12, U54.2, U$35.9, U$35.11
GND18: C217.2, C218.2, C219.2, C220.2, C221.2, C222.2, C223.2, C224.2, C225.2, C226.2, C228.2, JP91.3, R57.1, U55.1, U55.9, U55.11, U55.18, U56.2, U56.4, U56.5, U56.12, U57.2, U$37.9, U$37.11
GND19: C229.2, C230.2, C231.2, C232.2, C233.2, C234.2, C235.2, C236.2, C237.2, C238.2, C240.2, JP96.3, R60.1, U58.1, U58.9, U58.11, U58.18, U59.2, U59.4, U59.5, U59.12, U60.2, U$39.9, U$39.11
GND20: C241.2, C242.2, C243.2, C244.2, C245.2, C246.2, C247.2, C248.2, C249.2, C250.2, C252.2, JP101.3, R63.1, U61.1, U61.9, U61.11, U61.18, U62.2, U62.4, U62.5, U62.12, U63.2, U$41.9, U$41.11
GND21: C253.2, C254.2, C255.2, C256.2, C257.2, C258.2, C259.2, C260.2, C261.2, C262.2, C264.2, JP106.3, R66.1, U64.1, U64.9, U64.11, U64.18, U65.2, U65.4, U65.5, U65.12, U66.2, U$43.9, U$43.11
GND22: C265.2, C266.2, C267.2, C268.2, C269.2, C270.2, C271.2, C272.2, C273.2, C274.2, C276.2, JP111.3, R69.1, U67.1, U67.9, U67.11, U67.18, U68.2, U68.4, U68.5, U68.12, U69.2, U$45.9, U$45.11
GND23: C277.2, C278.2, C279.2, C280.2, C281.2, C282.2, C283.2, C284.2, C285.2, C286.2, C288.2, JP116.3, R72.1, U70.1, U70.9, U70.11, U70.18, U71.2, U71.4, U71.5, U71.12, U72.2, U$47.9, U$47.11
GND24: C289.2, C290.2, C291.2, C292.2, C293.2, C294.2, C295.2, C296.2, C297.2, C298.2, C300.2, JP121.3, R75.1, U73.1, U73.9, U73.11, U73.18, U74.2, U74.4, U74.5, U74.12, U75.2, U$49.9, U$49.11
GND25: C301.2, C302.2, C303.2, C304.2, C305.2, C306.2, C307.2, C308.2, C309.2, C310.2, C312.2, JP126.3, R78.1, U76.1, U76.9, U76.11, U76.18, U77.2, U77.4, U77.5, U77.12, U78.2, U$51.9, U$51.11
GND26: C313.2, C314.2, C315.2, C316.2, C317.2, C318.2, C319.2, C320.2, C321.2, C322.2, C324.2, JP131.3, R81.1, U79.1, U79.9, U79.11, U79.18, U80.2, U80.4, U80.5, U80.12, U81.2, U$53.9, U$53.11
GND27: C325.2, C326.2, C327.2, C328.2, C329.2, C330.2, C331.2, C332.2, C333.2, C334.2, C336.2, JP136.3, R84.1, U82.1, U82.9, U82.11, U82.18, U83.2, U83.4, U83.5, U83.12, U84.2, U$55.9, U$55.11
GND28: C337.2, C338.2, C339.2, C340.2, C341.2, C342.2, C343.2, C344.2, C345.2, C346.2, C348.2, JP141.3, R87.1, U85.1, U85.9, U85.11, U85.18, U86.2, U86.4, U86.5, U86.12, U87.2, U$57.9, U$57.11
GND29: C349.2, C350.2, C351.2, C352.2, C353.2, C354.2, C355.2, C356.2, C357.2, C358.2, C360.2, JP146.3, R90.1, U88.1, U88.9, U88.11, U88.18, U89.2, U89.4, U89.5, U89.12, U90.2, U$59.9, U$59.11
GND30: C361.2, C362.2, C363.2, C364.2, C365.2, C366.2, C367.2, C368.2, C369.2, C370.2, C372.2, JP151.3, R93.1, U91.1, U91.9, U91.11, U91.18, U92.2, U92.4, U92.5, U92.12, U93.2, U$61.9, U$61.11
GND31: C373.2, C374.2, C375.2, C376.2, C377.2, C378.2, C379.2, C380.2, C381.2, C382.2, C384.2, JP156.3, R96.1, U94.1, U94.9, U94.11, U94.18, U95.2, U95.4, U95.5, U95.12, U96.2, U$63.9, U$63.11
GND32: C385.2, C386.2, C387.2, C388.2, C389.2, C390.2, C391.2, C392.2, C393.2, C394.2, C396.2, JP161.3, R99.1, U97.1, U97.9, U97.11, U97.18, U98.2, U98.4, U98.5, U98.12, U99.2, U$65.9, U$65.11
GND33: C397.2, C398.2, C399.2, C400.2, C401.2, C402.2, C403.2, C404.2, C405.2, C406.2, C408.2, JP166.3, R102.1, U100.1, U100.9, U100.11, U100.18, U101.2, U101.4, U101.5, U101.12, U102.2, U$67.9, U$67.11
GND34: C409.2, C410.2, C411.2, C412.2, C413.2, C414.2, C415.2, C416.2, C417.2, C418.2, C420.2, JP171.3, R105.1, U103.1, U103.9, U103.11, U103.18, U104.2, U104.4, U104.5, U104.12, U105.2, U$69.9, U$69.11
GND35: C421.2, C422.2, C423.2, C424.2, C425.2, C426.2, C427.2, C428.2, C429.2, C430.2, C432.2, JP176.3, R108.1, U106.1, U106.9, U106.11, U106.18, U107.2, U107.4, U107.5, U107.12, U108.2, U$71.9, U$71.11
GND36: C433.2, C434.2, C435.2, C436.2, C437.2, C438.2, C439.2, C440.2, C441.2, C442.2, C444.2, JP181.3, R111.1, U109.1, U109.9, U109.11, U109.18, U110.2, U110.4, U110.5, U110.12, U111.2, U$73.9, U$73.11
GND37: C445.2, C446.2, C447.2, C448.2, C449.2, C450.2, C451.2, C452.2, C453.2, C454.2, C456.2, JP186.3, R114.1, U112.1, U112.9, U112.11, U112.18, U113.2, U113.4, U113.5, U113.12, U114.2, U$75.9, U$75.11
GND38: C457.2, C458.2, C459.2, C460.2, C461.2, C462.2, C463.2, C464.2, C465.2, C466.2, C468.2, JP191.3, R117.1, U115.1, U115.9, U115.11, U115.18, U116.2, U116.4, U116.5, U116.12, U117.2, U$77.9, U$77.11
GND39: C469.2, C470.2, C471.2, C472.2, C473.2, C474.2, C475.2, C476.2, C477.2, C478.2, C480.2, JP196.3, R120.1, U118.1, U118.9, U118.11, U118.18, U119.2, U119.4, U119.5, U119.12, U120.2, U$79.9, U$79.11
GND40: C481.2, C482.2, C483.2, C484.2, C485.2, C486.2, C487.2, C488.2, C489.2, C490.2, C492.2, JP201.3, R123.1, U121.1, U121.9, U121.11, U121.18, U122.2, U122.4, U122.5, U122.12, U123.2, U$81.9, U$81.11
GND41: C493.2, C494.2, C495.2, C496.2, C497.2, C498.2, C499.2, C500.2, C501.2, C502.2, C504.2, JP206.3, R126.1, U124.1, U124.9, U124.11, U124.18, U125.2, U125.4, U125.5, U125.12, U126.2, U$83.9, U$83.11
GND42: C505.2, C506.2, C507.2, C508.2, C509.2, C510.2, C511.2, C512.2, C513.2, C514.2, C516.2, JP211.3, R129.1, U127.1, U127.9, U127.11, U127.18, U128.2, U128.4, U128.5, U128.12, U129.2, U$85.9, U$85.11
GND43: C517.2, C518.2, C519.2, C520.2, C521.2, C522.2, C523.2, C524.2, C525.2, C526.2, C528.2, JP216.3, R132.1, U130.1, U130.9, U130.11, U130.18, U131.2, U131.4, U131.5, U131.12, U132.2, U$87.9, U$87.11
GND44: C529.2, C530.2, C531.2, C532.2, C533.2, C534.2, C535.2, C536.2, C537.2, C538.2, C540.2, JP221.3, R135.1, U133.1, U133.9, U133.11, U133.18, U134.2, U134.4, U134.5, U134.12, U135.2, U$89.9, U$89.11
GND45: C541.2, C542.2, C543.2, C544.2, C545.2, C546.2, C547.2, C548.2, C549.2, C550.2, C552.2, JP226.3, R138.1, U136.1, U136.9, U136.11, U136.18, U137.2, U137.4, U137.5, U137.12, U138.2, U$91.9, U$91.11
GND46: C553.2, C554.2, C555.2, C556.2, C557.2, C558.2, C559.2, C560.2, C561.2, C562.2, C564.2, JP231.3, R141.1, U139.1, U139.9, U139.11, U139.18, U140.2, U140.4, U140.5, U140.12, U141.2, U$93.9, U$93.11
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
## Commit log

2014-05-28 Brd/Sch file(s) upload
2014-06-02 Computer Change
2014-06-02 comp change
2015-04-03 Adding in git files, updating to current boards on SF, cleaning up README
2015-04-03 Mid revision work - NOT FUNCTIONAL
2015-04-05 Mid layout attempt
2015-04-06 Complete reroute-WIP
2015-04-06 horizontal orientation
2015-04-06 No airwires!
2015-04-08 BOARD PROTO LAYOUT
2015-04-09 Adding units note to measurements
2015-04-09 Updating for QC checks
2015-04-15 Changes from engineering review
2015-04-17 Fixing QC issues
2015-04-20 Swapping JP1 and JP3 names on parts
2016-01-06 created larger v15a panel
2016-05-20 2.0 Changes
    - Replaces all three 3-axis sensors with single chip solution (LSM9DS1).
    - Reduced board length from 1.3" to 1.0"
    - ±2/±4/±8/±16 g linear acceleration full scale
    - ±4/±8/±12/±16 gauss magnetic full scale
    - ±245/±500/±2000 dps angular rate full scale
2016-05-23 Updating minor silk changes
2016-05-26 QC Fixes
    -Updated VDD trace width to 20mil throughout.
    -Reduced overall length from 1.0" to 0.9".
2016-05-26 Fixing Trace Widths
    All traces entering the IC are now the same size.
2016-06-30 v20 Changes
    - Switch to micro fiducials for better clearances.
    - Changed default I2C addresses to ox1E and 0x6B to match example code
    for LSM9DS1 Breakout.
    - Moved "v20" bottom copper text to clear bottom silk
2016-06-30 Changed visible layer settings
2016-06-30 V21 Changes
    Changes since initial v20:
    - Switched to micro fiducials for better clearances
    - Changed default I2C addresses to 0x1E and 0x6B to match LSM9DS1
    breakout board example code
    - Moved version text on bottom copper to clear the bottom silk
2016-06-30 Approved DRC Errors
    Approving overlap errors for jumpers
2016-07-01 Moved fiducial away from C3
2016-07-06 Created panel v21
2016-07-27 Updating files names to follow standard
2016-08-11 Updating readme
    - updated image to new layout
    - updated link to product page
2016-08-11 Updating Readme
    Updated description with current sensor used and product dimensions
2016-08-11 Removed old sensors from Readme
